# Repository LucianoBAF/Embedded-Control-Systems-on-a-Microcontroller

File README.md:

# Electromagnetic control system on a microcontroller
Este repositório tem como funcionalidade armazenar os arquivos do projeto de controle de momvimento linear de uma bobina ao longo de um cilindro ferromagnético, operando em loop fechado. Abaixo há uma descrição de cada arquivo.
<table>
  <tr>
    <th>Nome do arquivo</th>
    <th>Descrição</th>
  </tr>
  <tr>
    <td>Bibliotecas Arduino.rar</td>
    <td>Biblioteca para utilização do Timer1 e leitura do sensor ultrassônica HC-SR04</td>
  </tr>
  <tr>
    <td>PRCSS_CSV.rar</td>
    <td>Programa em Processing para ler dados no padrão CSV via serial</td>
  </tr>
  <tr>
    <td>Projeto controle - Eagle.rar</td>
    <td>Projeto do eagle com esquemático e pcb</td>
  </tr>
  <tr>
    <td>YOUTUBE-Arduino - controlador geral.rar</td>
    <td>Todo material necessário para se controlar o projeto pelo Arduino</td>
  </tr>
  <tr>
    <td>YOUTUBE-Matlab e Arduino - Teste senoides.rar</td>
    <td>Todo material necessário para se obter a função de transferência do sistema através do teste das senoides</td>
  </tr>
  <tr>
    <td>motor_de_passo.rar</td>
    <td>Programa para arduino que controla um motor de passo desde um â inicial até 90º, depois até 0º e fica repetindo 0º a 90º</td>
  </tr>
    <tr>
    <td>projeto_eletromagnetismo.ino</td>
    <td>Projeto em arduino. Falta implementar contador para amostragens de controle iguais, além da lógica de manipulação de posição por joystick referente à parte de "um movimento até um extremo e posterior retorno ao centro do joystick" = alterção de 1cm. Além disso está pendente a comunicação entre arduino e matlab em tempo real </td>
  </tr>
    <tr>
    <td>projeto_eletromagnetismo_atmel.rar</td>
    <td>Projeto em Atmel Studio 7. Falta implementar contador para amostragens de controle iguais </td>
  </tr>
</table>

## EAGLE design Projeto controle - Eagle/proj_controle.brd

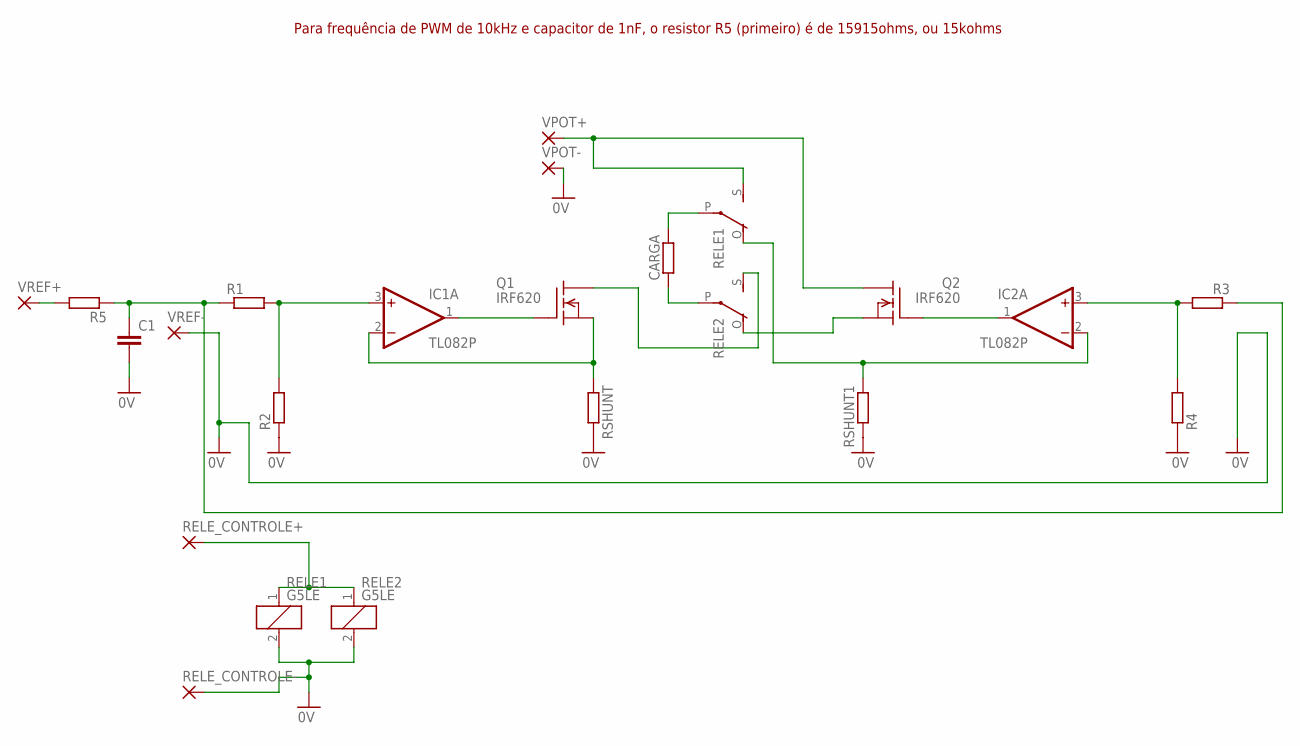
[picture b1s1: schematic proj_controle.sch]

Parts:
C1: C-EU050-025X075; C050-025X075
CARGA: R-EU_0207/10; 0207/10
IC1, IC2: TL082P; DIL08
Q1, Q2: IRF620; TO220
R1, R2, R3, R4, R5: R-EU_0207/10; 0207/10
RELE1, RELE2: G5LE
RELE_CONTROLE+: 3,17/1,1
RELE_CONTROLE-: 3,17/1,1
RSHUNT, RSHUNT1: R-EU_0617/22; 0617/22
VPOT+: 3,17/1,1
VPOT-: 3,17/1,1
VREF+: 3,17/1,1
VREF-: 3,17/1,1

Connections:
0V: C1.2, R2.1, R4.1, RELE1.2, RELE2.2, RELE_CONTROLE-.1, RSHUNT.2, RSHUNT1.2, VPOT-.1, VREF-.1
unnamed: CARGA.1, RELE2.P
unnamed: IC1.3 (+IN), R1.2, R2.2
unnamed: IC1.1 (OUT), Q1.1 (G)
unnamed: IC1.2 (-IN), Q1.3 (S), RSHUNT.1
unnamed: C1.1, R1.1, R3.1, R5.1
unnamed: R5.2, VREF+.1
unnamed: CARGA.2, RELE1.P
unnamed: Q1.2 (D), RELE2.S
unnamed: IC2.3 (+IN), R3.2, R4.2
unnamed: IC2.1 (OUT), Q2.1 (G)
unnamed: IC2.2 (-IN), RELE1.O, RSHUNT1.1
unnamed: Q2.2 (D), RELE1.S, VPOT+.1
unnamed: Q2.3 (S), RELE2.O
unnamed: RELE1.1, RELE2.1, RELE_CONTROLE+.1
V+: IC1.8 (V+), IC2.8 (V+)
V-: IC1.4 (V-), IC2.4 (V-)

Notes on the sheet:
Para frequência de PWM de 10kHz e capacitor de 1nF, o resistor R5 (primeiro) é de 15915ohms, ou 15kohms

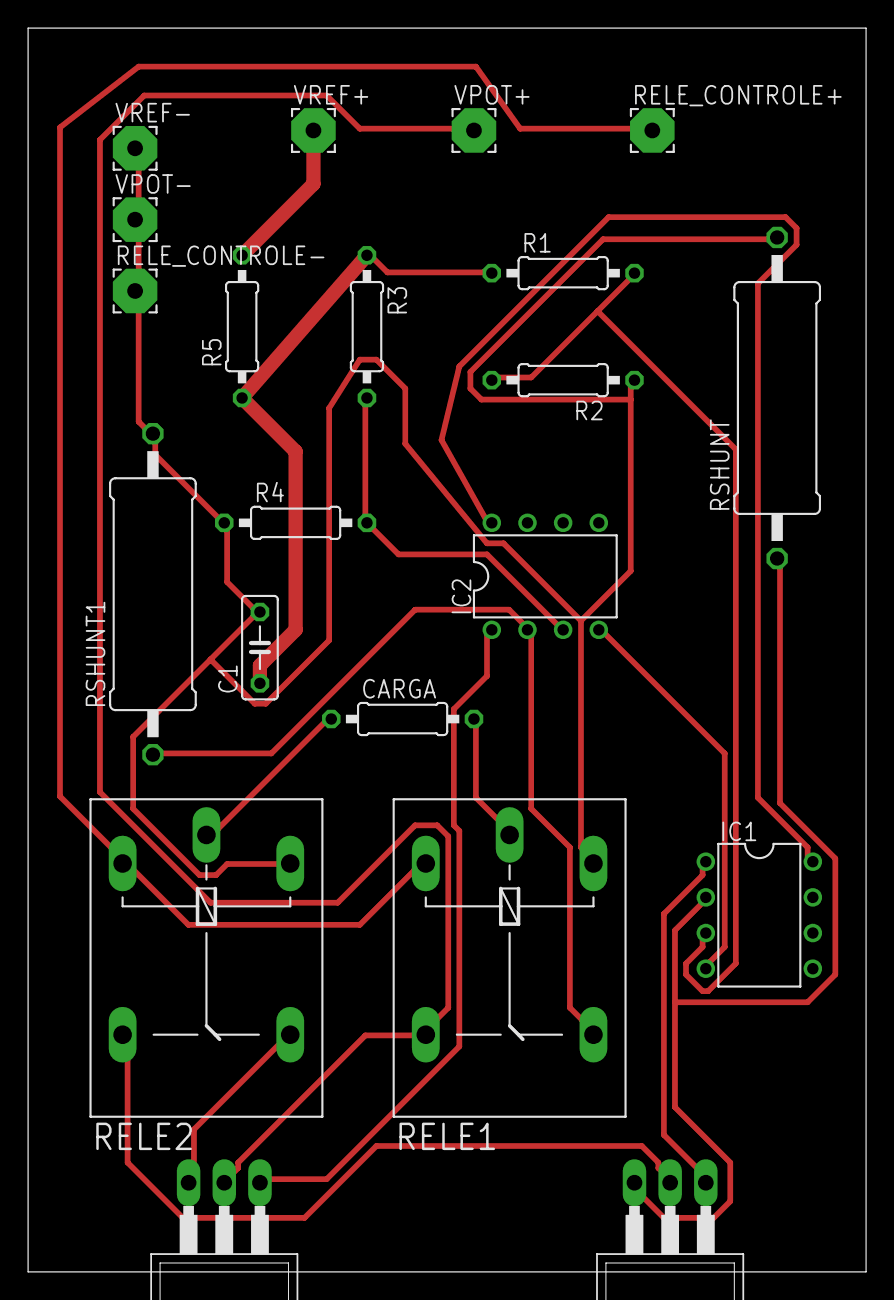
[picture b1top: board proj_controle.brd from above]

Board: 2 copper layers, 59.7 x 88.6 mm, 21 parts (0 on the bottom side), 17 nets.

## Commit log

2016-09-29 Create ARD_senoide_csv
    Escrita de um senoide, leitura do sensor ultrassônico e escrita de ambos na serial para gerar csv
2016-09-29 Biblioteca do timer1 para arduino
2016-09-29 Add files via upload
    Programa em Processing para leitura de dados via serial e escrita em arquivo CSV
2016-09-29 ARD_senoide_csv
    Programa para Arduino que gera uma senoide com o timer1, lê o valor do sensor ultrassônico e envia os dados para o Processing via serial para escrita em um arquivo csv
2016-09-29 ARD_senoide_ultrass_csv
2016-09-29 ARD_senoide_ultrassonic_csv
    Programa para Arduino que cria senoide, lê sensor ultrassônico e escreve valor na serial para o Processing gerar um CSV
2016-09-29 ARD_senoide_ultrass_csv
    Programa para Arduino que cria senoide, lê sensor ultrassônico e escreve valor na serial para o Processing gerar um CSV
2016-11-09 Adicionado resistor e capacitor pro PWM e melhorada a placa
2016-11-09 versão lixo
2016-11-15 Add files via upload
    Só uma fonte com controle de direção da corrente por ponte H.
    Placa pronta com plano terra e nomes
    Obs: versão do Eagle em casa: 7.6.0
2016-11-23 FEITO NO DAELE
2016-11-27 Versão primária Kahler
2016-11-27 Controla posição da bobina conforme potenciômetro em A0
    Não há certeza do funcionamento
